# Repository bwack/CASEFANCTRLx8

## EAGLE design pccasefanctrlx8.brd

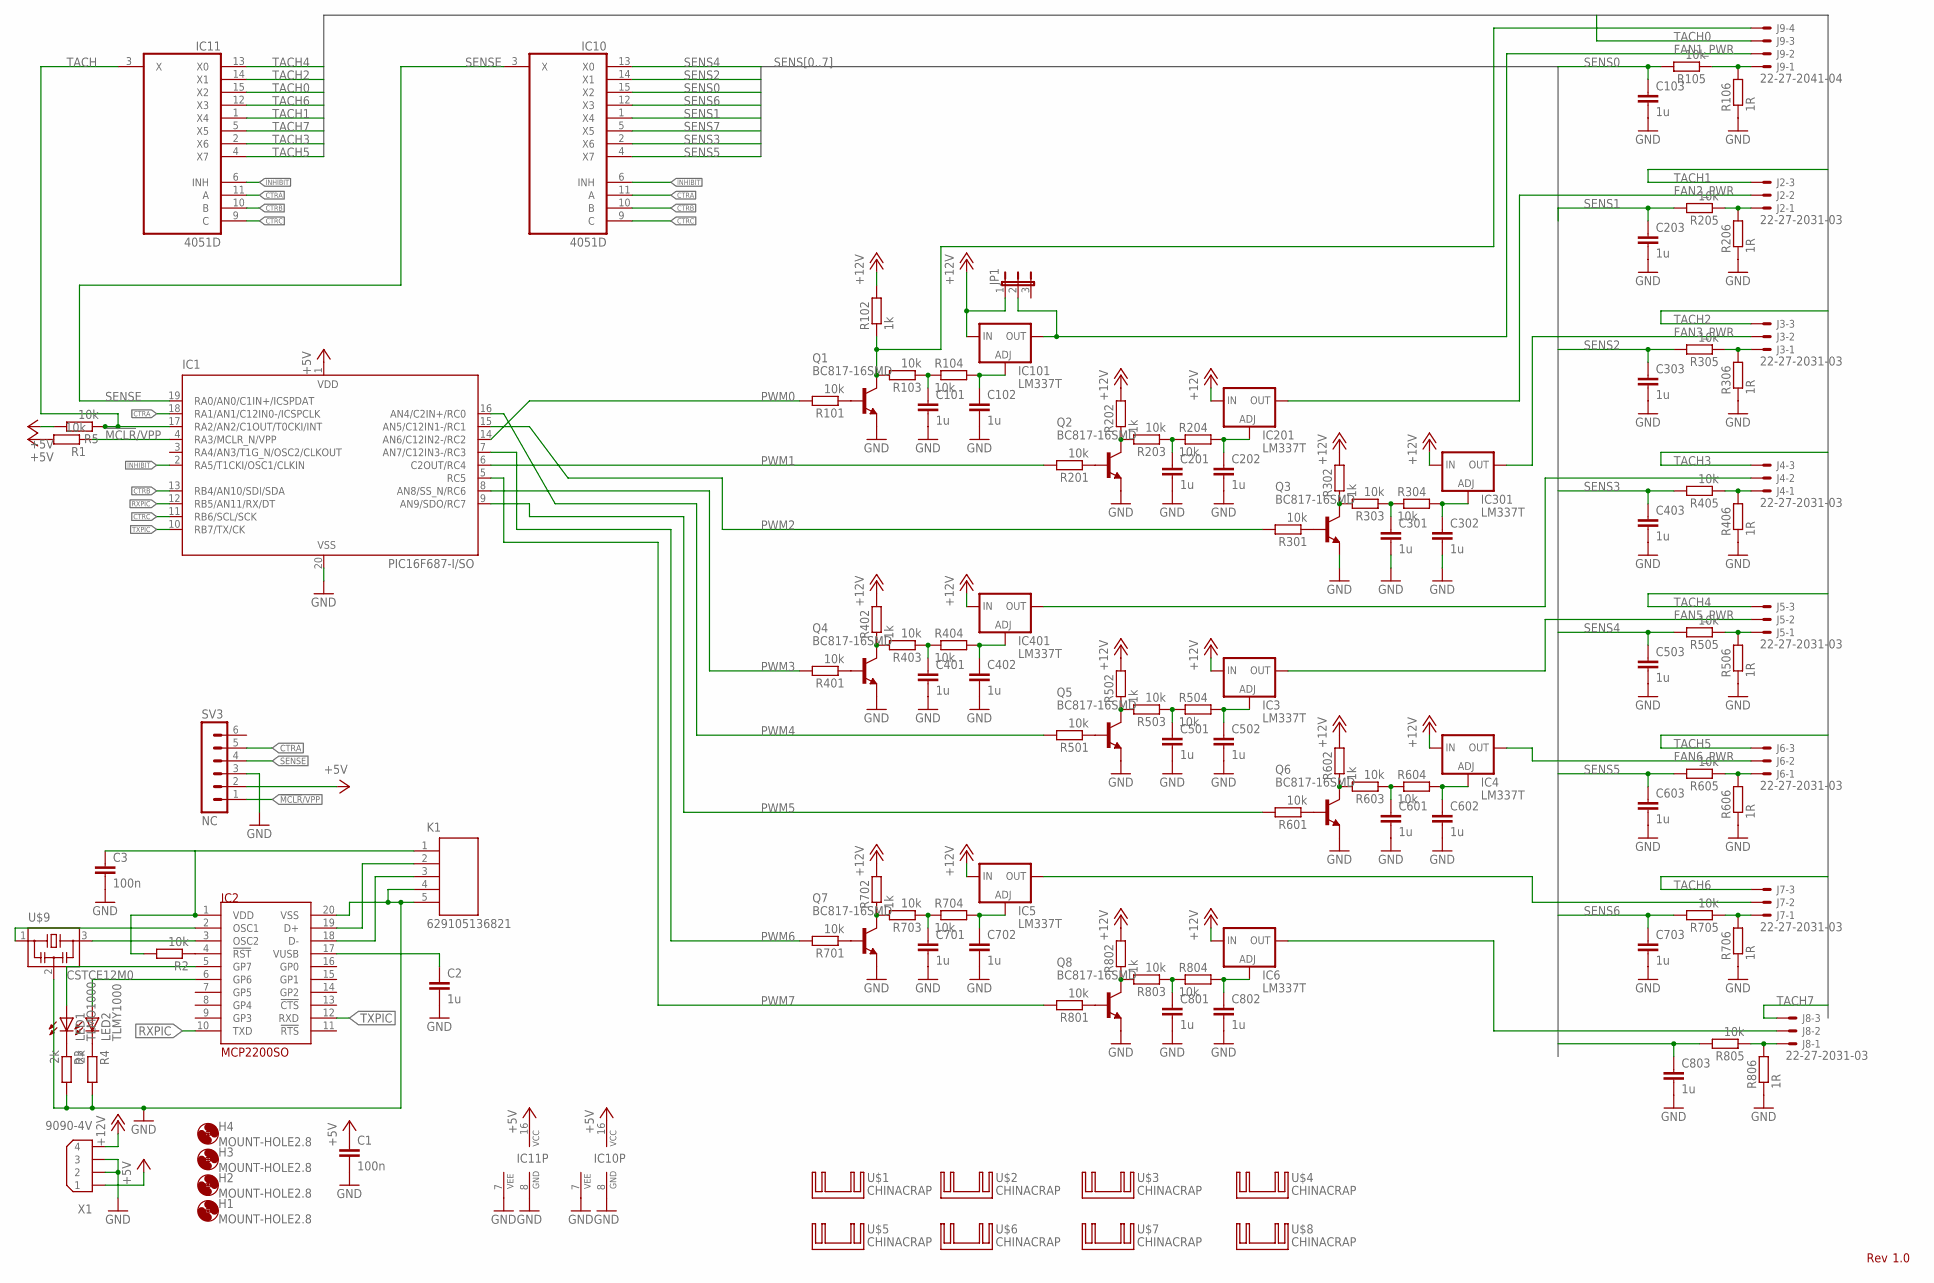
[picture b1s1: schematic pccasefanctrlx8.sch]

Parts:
C1, C3: 100n; C0603K
C2, C101, C102, C103, C201, C202, C203, C301, C302, C303, C401, C402, C403, C501, C502, C503, C601, C602, C603, C701, C702, C703, C801, C802, C803: 1u; C0603K
H1, H2, H3, H4: MOUNT-HOLE2.8; 2,8
IC1: PIC16F687-I/SO; SO-20W
IC2: MCP2200SO; SO-20W
IC3, IC4, IC5, IC6, IC101, IC201, IC301, IC401: LM337T; 317TS
IC10, IC11: 4051D; SO16
J2, J3, J4, J5, J6, J7, J8: 22-27-2031-03; 6410-03
J9: 22-27-2041-04; 6410-04
JP1: JP2E; JP2
K1: 629105136821
LED1: TLMO1000; SML0603
LED2: TLMY1000; SML0603
Q1, Q2, Q3, Q4, Q5, Q6, Q7, Q8: BC817-16SMD; SOT23-BEC
R1, R2, R5, R101, R103, R104, R105, R201, R203, R204, R205, R301, R303, R304, R305, R401, R403, R404, R405, R501, R503, R504, R505, R601, R603, R604, R605, R701, R703, R704, R705, R801, R803, R804, R805: 10k; R0603
R3, R4: 2k; R0603
R102, R202, R302, R402, R502, R602, R702, R802: 1k; R0603
R106, R206, R306, R406, R506, R606, R706, R806: 1R; P0613V
SV3: NC; MA06-1
U$1, U$2, U$3, U$4, U$5, U$6, U$7, U$8: CHINACRAP; MYCHINACRAP
U$9: CSTCE12M0; CSTCE_G
X1: 9090-4V

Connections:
!MCLR!/VPP: IC1.4 (RA3/MCLR_N/VPP), R1.1, SV3.1
+5V: C1.1, IC1.1 (VDD), IC10.16 (VCC), IC11.16 (VCC), R1.2, R5.2, SV3.2, X1.1
+12V: IC3.3 (IN), IC4.3 (IN), IC5.3 (IN), IC6.3 (IN), IC101.3 (IN), IC201.3 (IN), IC301.3 (IN), IC401.3 (IN), JP1.1, R102.2, R202.2, R302.2, R402.2, R502.2, R602.2, R702.2, R802.2, X1.4
CTRA: IC1.18 (RA1/AN1/C12IN0-/ICSPCLK), IC10.11 (A), IC11.11 (A), SV3.5
CTRB: IC1.13 (RB4/AN10/SDI/SDA), IC10.10 (B), IC11.10 (B)
CTRC: IC1.11 (RB6/SCL/SCK), IC10.9 (C), IC11.9 (C)
FAN1_PWR: IC101.2 (OUT), J9.2, JP1.2
FAN2_PWR: IC201.2 (OUT), J2.2
FAN3_PWR: IC301.2 (OUT), J3.2
FAN5_PWR: IC3.2 (OUT), J5.2
FAN6_PWR: IC4.2 (OUT), J6.2
GND: C1.2, C2.2, C3.2, C101.2, C102.2, C103.2, C201.2, C202.2, C203.2, C301.2, C302.2, C303.2, C401.2, C402.2, C403.2, C501.2, C502.2, C503.2, C601.2, C602.2, C603.2, C701.2, C702.2, C703.2, C801.2, C802.2, C803.2, IC1.20 (VSS), IC2.20 (VSS), IC10.7 (VEE), IC10.8 (GND), IC11.7 (VEE), IC11.8 (GND), K1.4, K1.5, Q1.E, Q2.E, Q3.E, Q4.E, Q5.E, Q6.E, Q7.E, Q8.E, R3.2, R4.2, R106.1, R206.1, R306.1, R406.1, R506.1, R606.1, R706.1, R806.1, SV3.3, U$9.2, X1.2, X1.3
INHIBIT: IC1.2 (RA5/T1CKI/OSC1/CLKIN), IC10.6 (INH), IC11.6 (INH)
unnamed: J9.4, Q1.C, R102.1, R103.2
unnamed: Q1.B, R101.1
unnamed: C201.1, R203.1, R204.1
unnamed: C101.1, R103.1, R104.1
unnamed: C102.1, IC101.1 (ADJ), R104.2
unnamed: C202.1, IC201.1 (ADJ), R204.2
unnamed: Q2.C, R202.1, R203.2
unnamed: Q2.B, R201.1
unnamed: J9.1, R105.1, R106.2
unnamed: J4.1, R405.1, R406.2
unnamed: C301.1, R303.1, R304.1
unnamed: C302.1, IC301.1 (ADJ), R304.2
unnamed: Q3.C, R302.1, R303.2
unnamed: Q3.B, R301.1
unnamed: C401.1, R403.1, R404.1
unnamed: C402.1, IC401.1 (ADJ), R404.2
unnamed: Q4.C, R402.1, R403.2
unnamed: Q4.B, R401.1
unnamed: IC401.2 (OUT), J4.2
unnamed: J2.1, R205.1, R206.2
unnamed: IC2.2 (OSC1), U$9.1
unnamed: IC2.3 (OSC2), U$9.3
unnamed: C3.1, IC2.1 (VDD), K1.1, R2.2
unnamed: IC2.4 (!RST!), R2.1
unnamed: IC2.18 (D-), K1.3
unnamed: IC2.19 (D+), K1.2
unnamed: IC2.5 (GP7), LED1.A
unnamed: C2.1, IC2.17 (VUSB)
unnamed: IC2.6 (GP6), LED2.A
unnamed: LED1.C, R3.1
unnamed: LED2.C, R4.1
unnamed: C501.1, R503.1, R504.1
unnamed: C502.1, IC3.1 (ADJ), R504.2
unnamed: Q5.C, R502.1, R503.2
unnamed: Q5.B, R501.1
unnamed: C601.1, R603.1, R604.1
unnamed: C602.1, IC4.1 (ADJ), R604.2
unnamed: Q6.C, R602.1, R603.2
unnamed: Q6.B, R601.1
unnamed: IC5.2 (OUT), J7.2
unnamed: C701.1, R703.1, R704.1
unnamed: C702.1, IC5.1 (ADJ), R704.2
unnamed: Q7.C, R702.1, R703.2
unnamed: Q7.B, R701.1
unnamed: C801.1, R803.1, R804.1
unnamed: C802.1, IC6.1 (ADJ), R804.2
unnamed: Q8.C, R802.1, R803.2
unnamed: Q8.B, R801.1
unnamed: IC6.2 (OUT), J8.2
unnamed: J3.1, R305.1, R306.2
unnamed: J6.1, R605.1, R606.2
unnamed: J7.1, R705.1, R706.2
unnamed: J8.1, R805.1, R806.2
unnamed: J5.1, R505.1, R506.2
PWM0: IC1.14 (AN6/C12IN2-/RC2), R101.2
PWM1: IC1.6 (C2OUT/RC4), R201.2
PWM2: IC1.15 (AN5/C12IN1-/RC1), R301.2
PWM3: IC1.8 (AN8/SS_N/RC6), R401.2
PWM4: IC1.16 (AN4/C2IN+/RC0), R501.2
PWM5: IC1.9 (AN9/SDO/RC7), R601.2
PWM6: IC1.7 (AN7/C12IN3-/RC3), R701.2
PWM7: IC1.5 (RC5), R801.2
RXPIC: IC1.12 (RB5/AN11/RX/DT), IC2.10 (TXD)
SENS0: C103.1, IC10.15 (X2), R105.2
SENS1: C203.1, IC10.1 (X4), R205.2
SENS2: C303.1, IC10.14 (X1), R305.2
SENS3: C403.1, IC10.2 (X6), R405.2
SENS4: C503.1, IC10.13 (X0), R505.2
SENS5: C603.1, IC10.4 (X7), R605.2
SENS6: C703.1, IC10.12 (X3), R705.2
SENS7: C803.1, IC10.5 (X5), R805.2
SENSE: IC1.19 (RA0/AN0/C1IN+/ICSPDAT), IC10.3 (X), SV3.4
TACH: IC1.17 (RA2/AN2/C1OUT/T0CKI/INT), IC11.3 (X), R5.1
TACH0: IC11.15 (X2), J9.3
TACH1: IC11.1 (X4), J2.3
TACH2: IC11.14 (X1), J3.3
TACH3: IC11.2 (X6), J4.3
TACH4: IC11.13 (X0), J5.3
TACH5: IC11.4 (X7), J6.3
TACH6: IC11.12 (X3), J7.3
TACH7: IC11.5 (X5), J8.3
TXPIC: IC1.10 (RB7/TX/CK), IC2.12 (RXD)

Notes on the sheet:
Rev

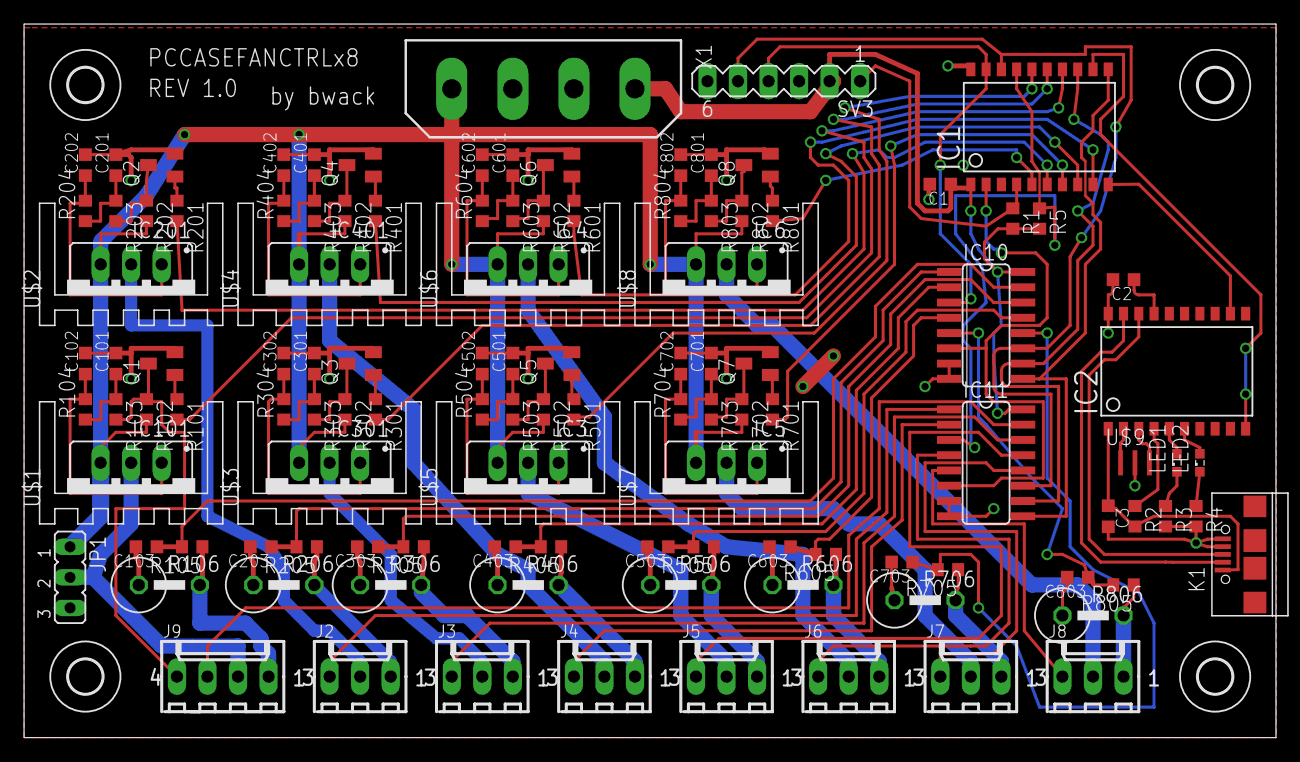
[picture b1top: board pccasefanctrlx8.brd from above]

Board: 2 copper layers, 104.1 x 59.4 mm, 127 parts (0 on the bottom side), 95 nets.

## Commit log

2015-03-08 :confetti_ball: Added .gitattributes & .gitignore files
2016-09-14 first commit, old stuff

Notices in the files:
parts and their libraries:
USBSteckverbinderWR-COM: Copyright: Würth Elektronik
